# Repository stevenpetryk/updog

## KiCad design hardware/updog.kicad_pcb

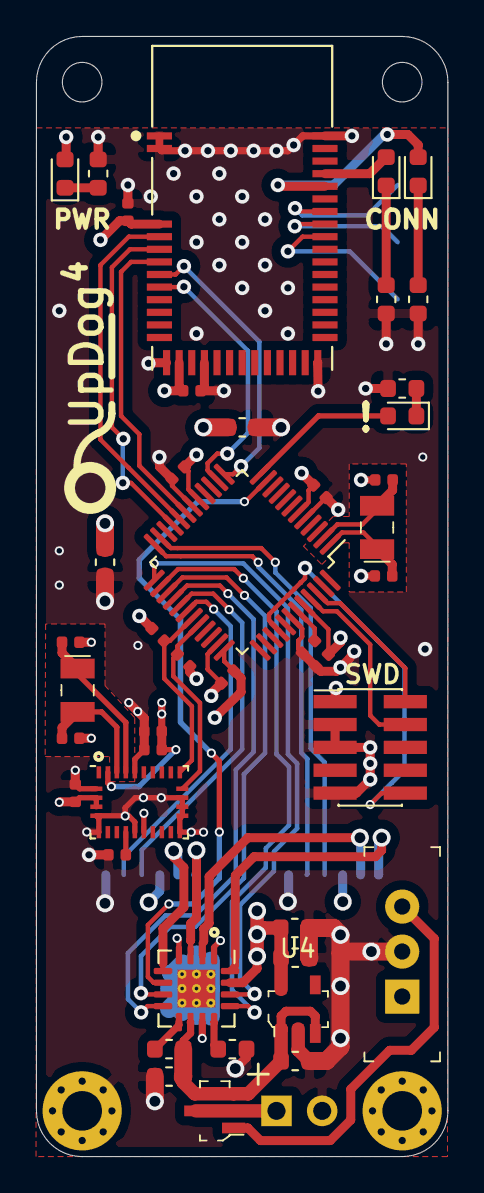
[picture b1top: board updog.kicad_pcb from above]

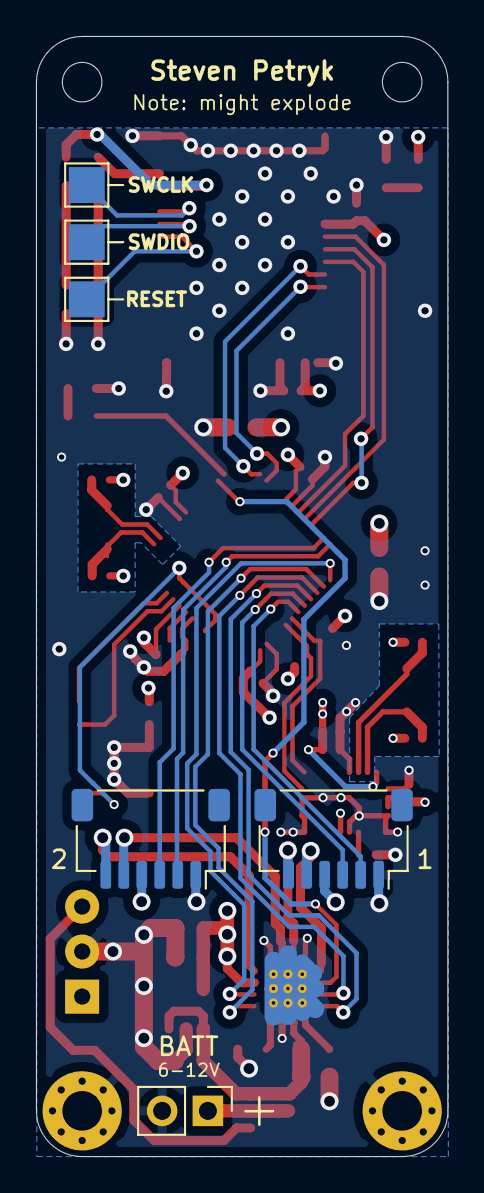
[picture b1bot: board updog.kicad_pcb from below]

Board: 4 copper layers, 22.9 x 62.2 mm, 53 parts (6 on the bottom side), 46 nets.

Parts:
BATT1: Conn_01x02; PinHeader_1x02_P2.54mm_Vertical
C1, C8, C13, C17, C19: 10µ; C_0603_1608Metric
C2, C6, C7, C10, C14, C21, C22: 0.1µ; C_0402_1005Metric
C3: 1µ; C_0402_1005Metric
C4, C5, C15, C16: 15p; C_0402_1005Metric
C9, C11: 10µ; C_0402_1005Metric
C12: 6.8n; C_0402_1005Metric
C18: 0.01µ; C_0603_1608Metric
C20: 2.2µ, 6.3V; C_0603_1608Metric
C23: 1µ; C_0603_1608Metric
D1, D3: Blue; LED_0603_1608Metric
D2, D4: Red; LED_0603_1608Metric
H1, H2: MountingHole; MountingHole_2.2mm_M2
H3, H4: MountingHole_Pad; MountingHole_2.2mm_M2_Pad_Via
J1: JTAG Debugger; PinHeader_2x05_P1.27mm_Vertical_SMD
J2, J3: Conn_01x06; JST_SH_SM06B-SRSS-TB_1x06-1MP_P1.00mm_Horizontal
Q1: DMG2305UX-13; SOT-23-3
R1: 100; L_0603_1608Metric
R2, R3, R6: 100; R_0603_1608Metric
R4, R5: 10k; R_0402_1005Metric
S1: EG1218; Switch_Slide_11.6x4mm_EG1218
TP1, TP2, TP3: TestPoint; TestPoint_Pad_2.0x2.0mm
U1: ATSAMD21G18; LQFP-48_7x7mm_P0.5mm
U2: MDBT40-256RV3; MODULE_MDBT40-256RV3
U3: BNO055; LGA-28_5.2x3.8mm_P0.5mm
U4: MIC5219-3_3YM5-TR; SOT-753
U5: DRV8833RTY; Texas_S-PWQFN-N16_EP2.1x2.1mm_ThermalVias
XTAL1, XTAL2: 32.768kHz; SMD-2_3.2x1.5mm

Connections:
+3V3: C1.2, C2.2, C6.2, C7.2, C8.2, C9.1, C10.2, C11.1, C12.1, C17.2, C21.1, C22.1, C23.2, D2.2, J1.1, J2.4, J3.4, R4.1, R5.1, U1.6, U1.17, U1.36, U1.44, U2.3, U2.14, U3.3, U3.4, U3.11, U3.28, U4.5, U5.15
+BATT: C13.2, C18.2, C19.1, Q1.2, U4.1, U4.3, U5.10
/AIN1: U1.25, U5.14
/AIN2: U1.26, U5.13
/BIN1: U1.27, U5.7
/BIN2: U1.28, U5.8
/BT_CONN: D3.2, U2.39
/BT_MODE: D1.2, U2.38
/D21_LED: D4.2, U1.12
/DRV_FAULT: U1.11, U5.6
/ENC1A: J2.2, U1.30
/ENC1B: J2.3, U1.29
/ENC2A: J3.2, U1.24
/ENC2B: J3.3, U1.23
/M1A: J2.5, U5.5
/M1B: J2.6, U5.3
/M2A: J3.5, U5.2
/M2B: J3.6, U5.16
/MISO: U1.21, U2.5
/MOSI: U1.19, U2.6
/NRF_CS: U1.13, U2.7
/NRF_IRQ: U1.14, U2.8
/NRF_RESET: TP3.1, U2.34
/NRF_SWCLK: TP1.1, U2.36
/NRF_SWDIO: TP2.1, U2.35
/SCK: U1.20, U2.4
/SCL: R5.2, U1.32, U3.19
/SDA: R4.2, U1.31, U3.20
/SWDCLK: J1.4, U1.45
/SWDIO: J1.2, U1.46
/~RESET: J1.10, U1.40
GND: BATT1.2, C1.1, C2.1, C3.1, C4.2, C5.2, C6.1, C7.1, C8.1, C9.2, C10.1, C11.2, C12.2, C13.1, C14.2, C15.1, C16.1, C17.1, C19.2, C20.2, C21.2, C22.2, C23.1, H3.1, H4.1, J1.3, J1.5, J1.9, J2.1, J3.1, R1.2, R2.2, R3.2, R6.2, S1.2, U1.5, U1.18, U1.35, U1.42, U2.1, U2.2, U2.13, U2.16, U2.25, U2.42, U3.2, U3.5, U3.6, U3.10, U3.15, U3.16, U3.17, U3.18, U3.25, U4.2, U5.1, U5.4, U5.11, U5.17
unnamed: BATT1.1, Q1.3
unnamed: C3.2, U1.43
unnamed: C4.1, U1.1, XTAL1.1
unnamed: C5.1, U1.2, XTAL1.2
unnamed: C14.1, U3.9
unnamed: C15.2, U3.26, XTAL2.1
unnamed: C16.2, U3.27, XTAL2.2
unnamed: C18.1, U5.9
unnamed: C20.1, U5.12
unnamed: D1.1, R1.1
unnamed: D2.1, R2.1
unnamed: D3.1, R3.1
unnamed: D4.1, R6.1
unnamed: Q1.1, S1.3

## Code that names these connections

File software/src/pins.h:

#define DEBUG_LED 9

// Bluefruit connectivity
#define NRF_CS 4
#define NRF_IRQ 3

// Monitoring the DRV8833 motor driver
#define DRV_FAULT 8

// Motors
#define A_MOTOR_1 11
#define A_MOTOR_2 13
#define B_MOTOR_1 10
#define B_MOTOR_2 12

// Encoders
#define A_ENCODER_1 7
#define A_ENCODER_2 6
#define B_ENCODER_1 5
#define B_ENCODER_2 2

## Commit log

2020-07-25 Consolidate project: v4
2020-07-25 Initial setup with some classes
2020-07-25 Build out basics of motor output
